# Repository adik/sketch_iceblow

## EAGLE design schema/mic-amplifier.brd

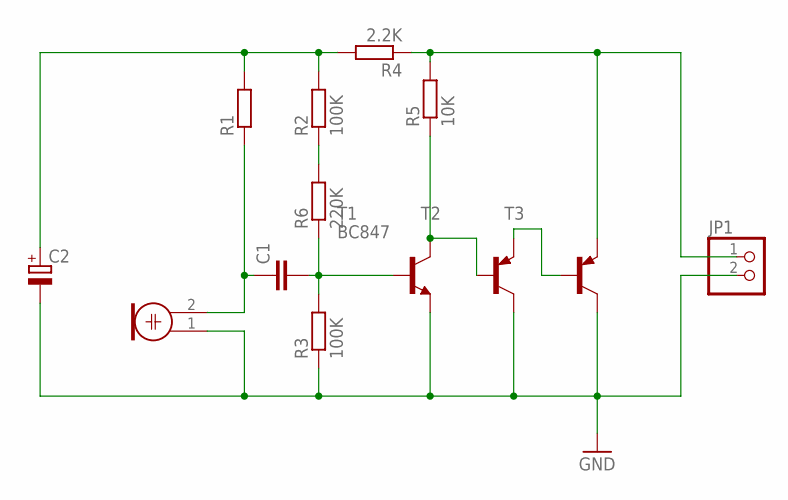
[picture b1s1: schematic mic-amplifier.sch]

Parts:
C1: C-EUC1206; C1206
C2: CPOL-EUE2,5-6E; E2,5-6E
JP1: PINHD-1X2; 1X02
M1: ELECTRET_MICROPHON-WM-61B; WM-61B
R1: R-EU_R0805; R0805
R2, R3: 100K; R0805
R4: 2.2K; R1206
R5: 10K; R1206
R6: 220K; R1206
T1: BC847; SOT23
T2, T3: BC857B-PNP-SOT23-BEC; SOT23-BEC

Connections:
GND: C2.-, JP1.2, M1.1, R3.1, T1.2 (E), T2.C, T3.C
unnamed: C2.+, R1.2, R2.2, R4.2
unnamed: C1.2, R3.2, R6.1, T1.1 (B)
unnamed: C1.1, M1.2, R1.1
unnamed: R2.1, R6.2
unnamed: R5.1, T1.3 (C), T2.B
unnamed: JP1.1, R4.1, R5.2, T3.E
unnamed: T2.E, T3.B

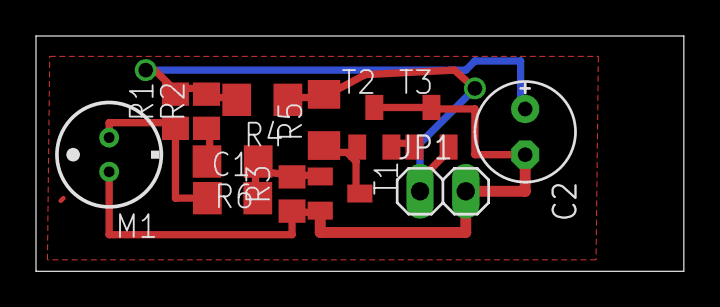
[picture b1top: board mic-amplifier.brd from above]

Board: 2 copper layers, 36.0 x 13.1 mm, 13 parts (0 on the bottom side), 8 nets.

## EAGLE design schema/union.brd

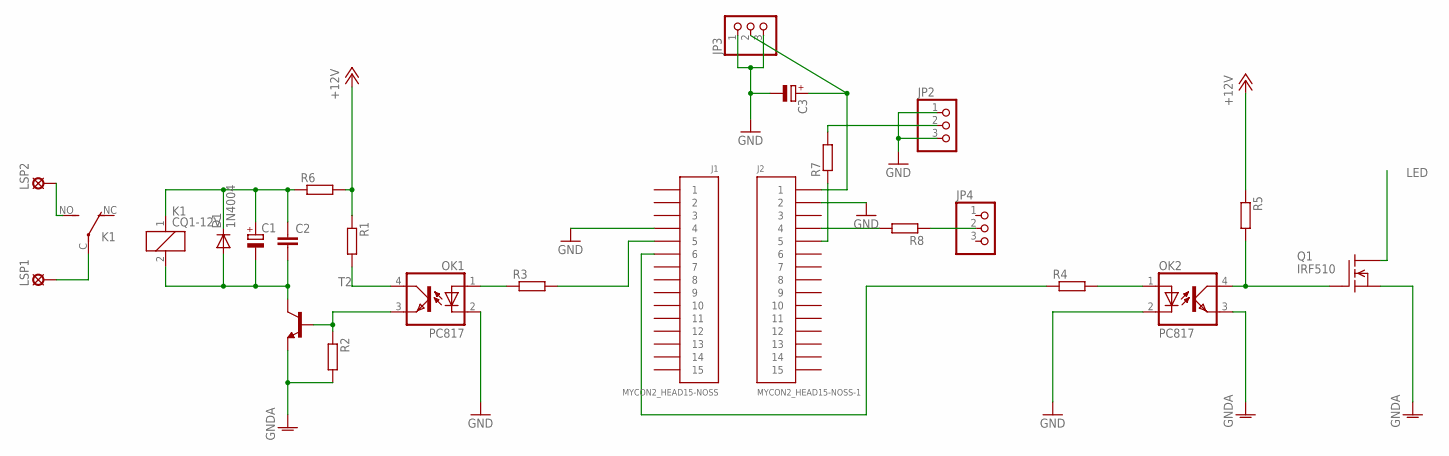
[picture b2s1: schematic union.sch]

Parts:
C1, C3: CPOL-EUE3.5-8; E3,5-8
C2: C-EUC1206; C1206
D1: 1N4004; DO41-10
J1: MYCON2_HEAD15-NOSS
J2: MYCON2_HEAD15-NOSS-1
JP2, JP3, JP4: PINHD-1X3; 1X03
K1: CQ1-12V; CQ1
LSP1, LSP2: LSP10
OK1, OK2: PC817; DIL04
Q1: IRF510; TO220
R1, R2, R3, R4, R5, R7, R8: R-EU_R1206; R1206
R6: R-EU_0204/5; 0204/5
T2: -NPN-TO92; TO92

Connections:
+12V: R1.1, R5.1, R6.2
GND: C3.-, J1.4, J2.2, JP2.1, JP2.3, JP3.1, JP3.3, OK1.2 (C), OK2.2 (C)
GNDA: OK2.3 (EMIT), Q1.3 (S), R2.2, T2.1 (E)
LED: Q1.2 (D)
unnamed: OK1.3 (EMIT), R2.1, T2.2 (B)
unnamed: C1.-, C2.2, D1.A, K1.2, T2.3 (C)
unnamed: OK1.4 (COL), R1.2
unnamed: OK1.1 (A), R3.1
unnamed: J1.6, R4.1
unnamed: K1.C, LSP1.MP
unnamed: K1.NO (S), LSP2.MP
unnamed: OK2.4 (COL), Q1.1 (G), R5.2
unnamed: OK2.1 (A), R4.2
unnamed: J1.5, R3.2
unnamed: C1.+, C2.1, D1.C, K1.1, R6.1
unnamed: JP2.2, R7.2
unnamed: J2.4, R8.2
unnamed: C3.+, J2.1, JP3.2
unnamed: J2.5, R7.1
unnamed: JP4.2, R8.1

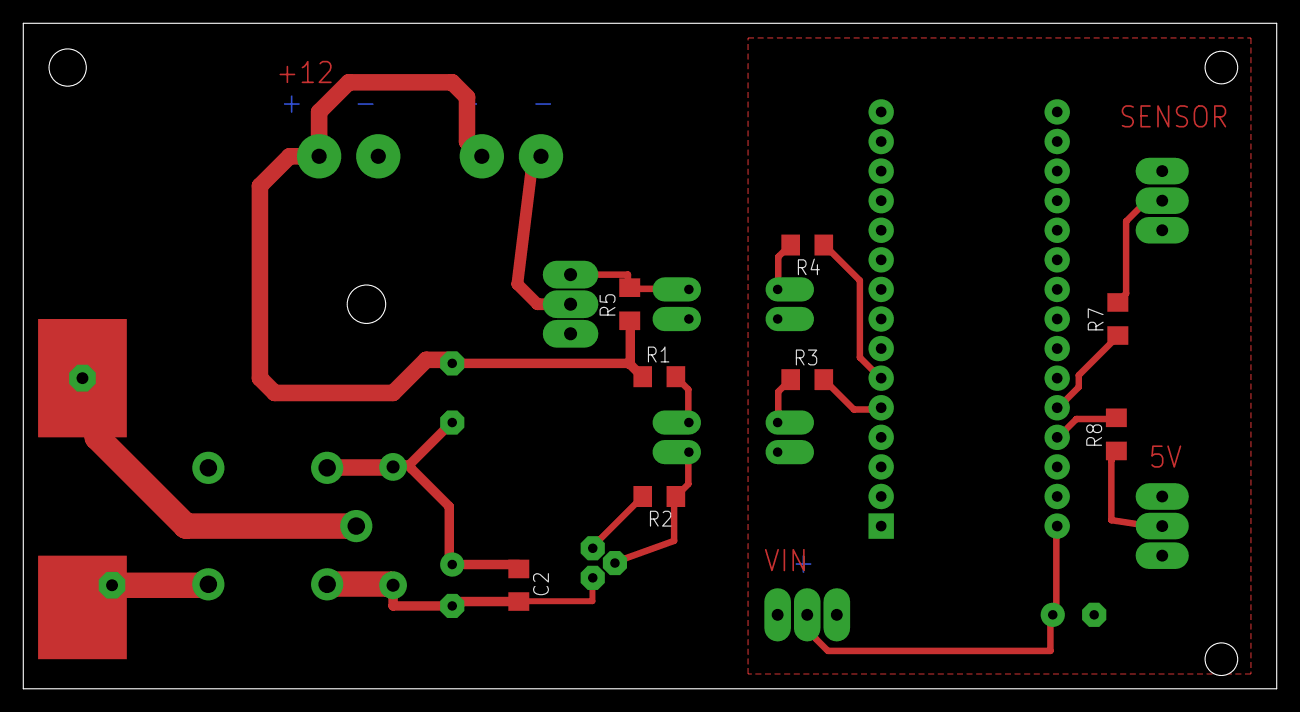
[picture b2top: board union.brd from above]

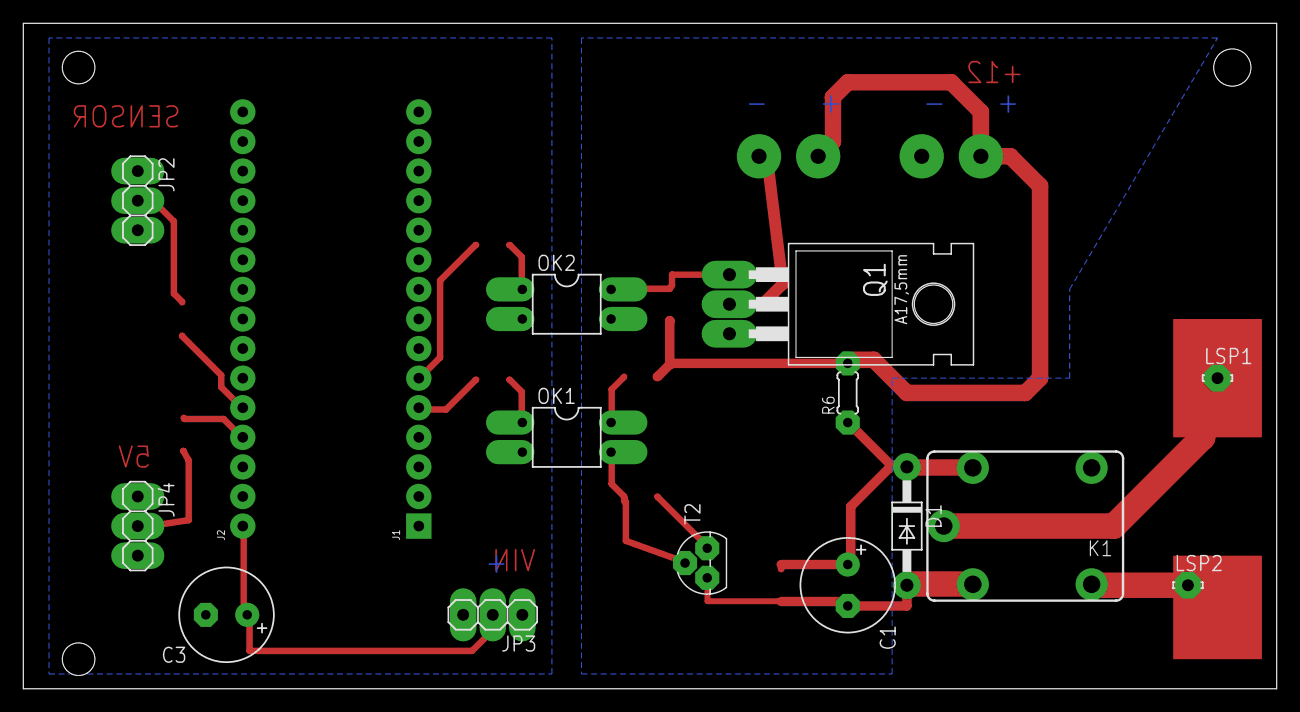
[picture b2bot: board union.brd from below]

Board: 2 copper layers, 107.6 x 57.1 mm, 24 parts (16 on the bottom side), 19 nets.

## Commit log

2014-12-25 Release project
